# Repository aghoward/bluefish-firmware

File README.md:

# bluefish password manager

bluefish is a hardware based password manager made to be easily transportable, cheap,
and secure.

## What's in this repository?

This repository contains the firmware and KiCad / Gerber files necessary for the hardware
to work. The hardware is based on the Arduino platform and requires some libraries from
the official Arduino standard library. You'll also need a few supporting libraries from
my own collection: [STL](https://github.com/aghoward/stl) and 
[either](https://github.com/aghoward/either). These will both need to be installed along
side other arduino libraries for the compiler to find them.

A make file has been provided which should allow you to compile the code for your atmel
chip; out of the box you can specify one of the following: `UNO=true`, `LEONARDO=true`,
`NANO=true`, or `MIGHTY1284P` to build for a specific platform. The most tested of these
is the UNO platform which is a atmel ATMega328P.

You can use `make` to build the code; and `make up` to use avrdude to flash the firmware
to your atmel chip. Have a look inside the hardware folder to find the wiring schematics
and all files necessary to print your own PCBs.

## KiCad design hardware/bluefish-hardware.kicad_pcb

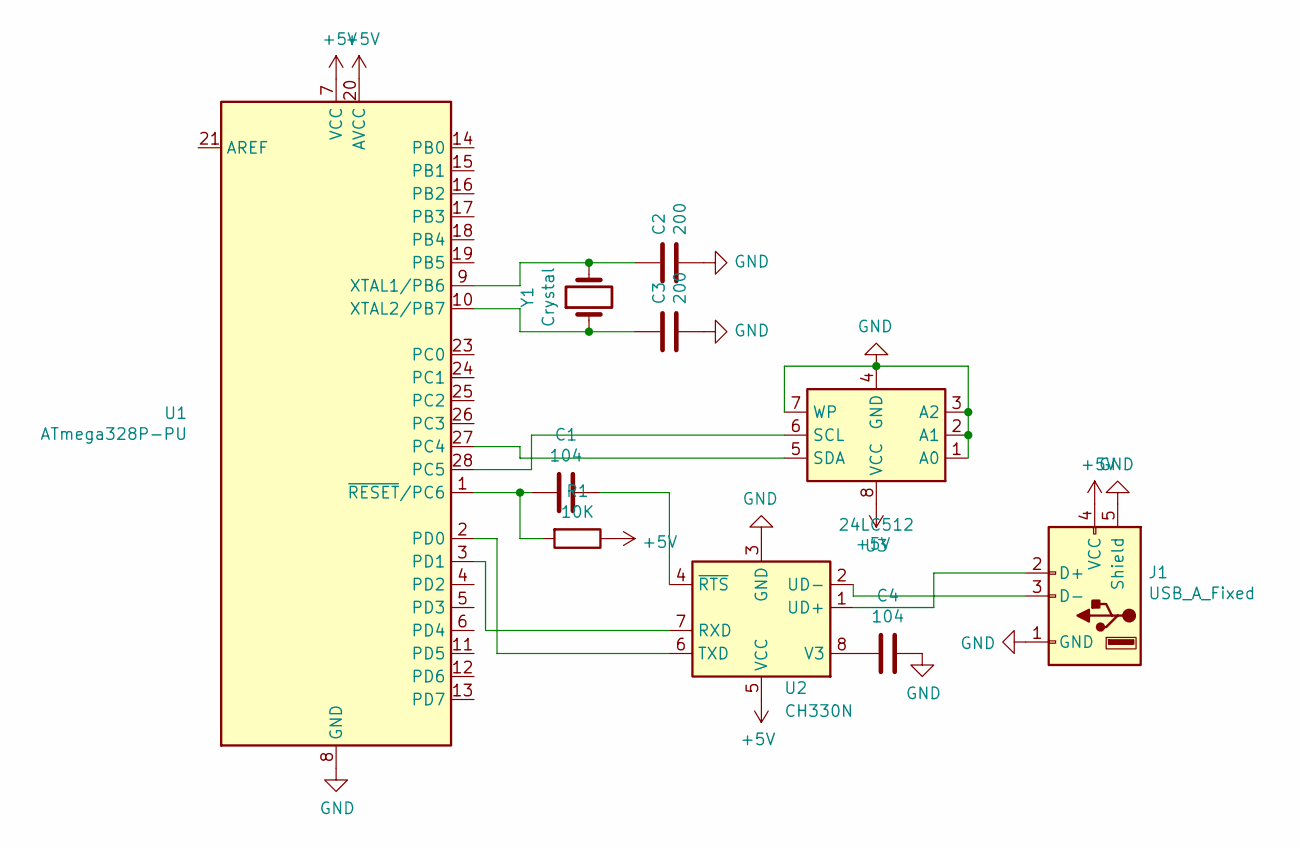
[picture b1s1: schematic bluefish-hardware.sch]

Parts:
C1, C4: 104; C_Rect_L7.0mm_W3.5mm_P5.00mm
C2, C3: 200; C_Rect_L7.0mm_W3.5mm_P5.00mm
J1: USB_A_Fixed; USB_A_Stewart_SS-52100-001_Horizontal
R1: 10K; R_Axial_DIN0207_L6.3mm_D2.5mm_P7.62mm_Horizontal
U1: ATmega328P-PU; DIP-28_W7.62mm
U2: CH330N; SOIC-8_3.9x4.9mm_P1.27mm
U3: 24LC512; DIP-8_W7.62mm_Socket
Y1: Crystal; Crystal_HC49-4H_Vertical

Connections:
+5V: J1.4 (VCC), R1.1, U1.7 (VCC), U1.20 (AVCC), U2.5 (VCC), U3.8 (VCC)
GND: C2.2, C3.2, C4.2, J1.1 (GND), J1.5 (Shield), U1.8 (GND), U1.22 (GND), U2.3 (GND), U3.1 (A0), U3.2 (A1), U3.3 (A2), U3.4 (GND), U3.7 (WP)
unnamed: C1.1, R1.2, U1.1 (~RESET~/PC6)
unnamed: C1.2, U2.4 (~RTS)
unnamed: C2.1, U1.9 (XTAL1/PB6), Y1.2
unnamed: C3.1, U1.10 (XTAL2/PB7), Y1.1
unnamed: C4.1, U2.8 (V3)
unnamed: J1.2 (D+), U2.1 (UD+)
unnamed: J1.3 (D-), U2.2 (UD-)
unnamed: U1.2 (PD0), U2.6 (TXD)
unnamed: U1.3 (PD1), U2.7 (RXD)
unnamed: U1.27 (PC4), U3.5 (SDA)
unnamed: U1.28 (PC5), U3.6 (SCL)

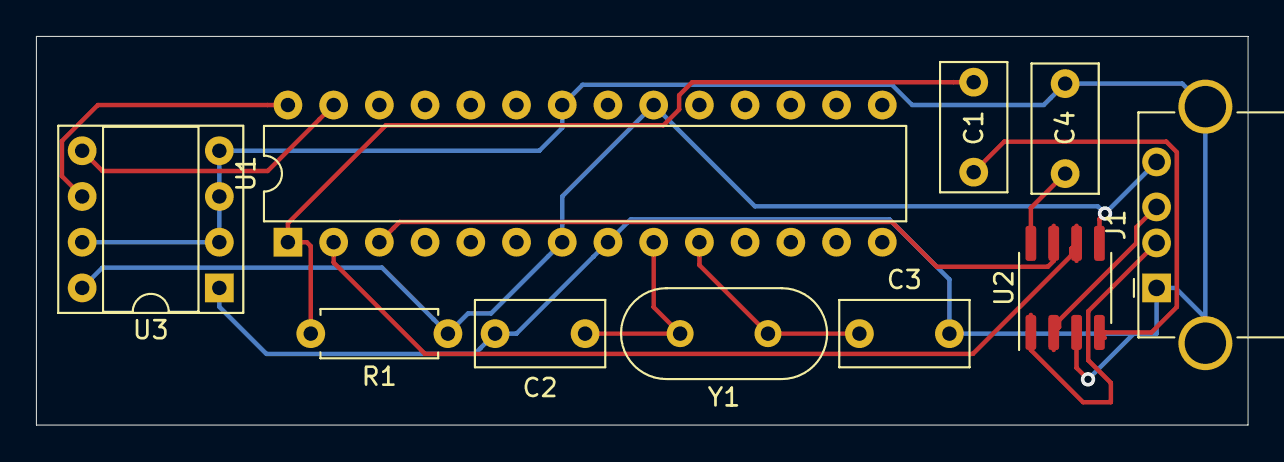
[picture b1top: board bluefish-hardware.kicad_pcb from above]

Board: 2 copper layers, 67.3 x 21.6 mm, 10 parts (0 on the bottom side), 13 nets.

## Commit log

2019-04-13 Initial Attempt
    Adds the basics for reading / writing the EEPROM (24LC16B) as a
    continous block of memory.
    Adds a simple filesystem that works for name, username, password
    combinations. Can read and list files by name.
    Adds STL like vector, probably not good enough to include in the STL
    implementation
2019-04-23 Make ATMEGA1284p Default target
2019-04-25 Improve Copies in CharString
    previously these methods were using a handrolled solution instead of
    properly using `memcpy`
2019-04-25 Dedupe logic in Filesystem
2019-04-25 Extract Method For Prompting User
    Adds a method for prompting the user for input
2019-04-25 Add Remove File
    Adds ability to remove a file by filename
2019-04-25 Fix Memory Corruption Bug
    Some places in the code were using `unsigned long` to attempt to
    construct a `CharString` of a given size; however, the only available
    signature was for `unsigned int` which caused the long to convert to
    `const char *` and construct an empty unitialized `CharString`. Adds a
    casting constructor for `unsigned long`
2019-06-17 Implement API objects
    Moves the majority of the logic out of the `eeprom.ino` file and into an
    API object. Retains the old communication mechanism as a `TextAPI` and
    implements a new API as a binary protocol.
    Additionally, fixed an SRP violation in `FileSystem` where it was
    directly communicating with the serial interface to provide usage
    statistics
2019-11-07 Fix Broken Makefile clean Target
2019-11-07 Update Binary API
    Makes each command send a ready byte to the other end to signal it is
    ready to receive data if necessary, and to act as an OK signal for the
    other end.
    Marks all methods in the binary api `override` to increase visibility
    into potential bugs.
2019-11-07 Minor Updates to SerialStream
    Force `SerialStream::read` to wait for available data before attempting
    to read, this prevents bad data from being read from the stream and
    other related bugs.
    Force `SerialStream::write` to flush data which makes us wait until
    things are written before continuing with execution
2019-11-07 Give project a proper name
    Project has been renamed, for too long this was simply called
    "eeprom-filesystem" it is much more than that now. It has been renamed
    "bluefish" with this hardware based component getting the name
    "bluefish-firmware". Bluefish is inspired by the name of the encryption
    algorithm to be used on the client side, "Twofish", and a play on Dr.
    Seuss' story "One fish two fish red fish blue fish".
2019-11-07 Store Encryption IV in Master Block
    The format call now requires an encryption IV to be stored in the master
    block. This allows creating unique IV's per format.
    Required making `CharString` copyable, though this should still be used
    sparingly.
    Renames `print_usage` to `get_master_block` to better describe what's
    actually happening
2019-11-07 Upgrade Filesystem
    Updates filesystem to allow bigger storage devices
2019-11-12 Implement Larger EEPROM
    Implements a driver for a larger EEPROM, the 24lc512, while still
    allowing the older 24lc16b to be used.
2019-11-12 Optimize Stream Integral Output
    Previously this copied each byte individually to the stream, when it
    could have just taken advantage of `memcpy` to do the copy in a single
    operation
2019-11-15 Remove the TextAPI
    This was rotting and I don't want to maintain it anymore
2019-11-15 Update API to Use IDs instead of strings
    Previously strings were being used for unique identification, but this
    is problematic for MCUs with smaller amounts of RAM, and also stringly
    typed things are bad.
2019-11-17 Fix EEPROM Bug
    Fixes issue in the 24lc512 EEPROM which caused invalid accesses if
    trying to write past the first page
2019-11-17 Add Challenge to Master Block
    Adds an encryption challenge to the master block so that we can verify
    the master password without storing it.
    Removes the `length` field from inodes as this is no longer used (if it
    ever was used).
2020-01-29 Simplify Binary API Read For Callers
    Previously a caller was expected to get a list of all file ids and read
    each one's filename individually to see if matched the filename they
    were looking for. This has been improved to only ask the caller to
    encrypt the filename first, send it to the device and the device will
    return the appropriate file after finding it by name.
2020-03-06 Add First Hardware Revision
    Adds all kicad and gerber files for the first revision of DIP and
    through-hole boards.
2020-03-06 Add README
    Adds a short readme to explain what this repository is
2021-08-26 Update either Library
    updates <either.h> version that's being used to the latest master (API
    change)
2022-09-24 Update Either API
    Switches to updated either library which had an API change.
2022-09-24 Increase I2C Bus Speed
    The EEPROM supports a max speed of 400KHZ. Now that the memory issues
    are resolved the device can comfortably run at that speed.
